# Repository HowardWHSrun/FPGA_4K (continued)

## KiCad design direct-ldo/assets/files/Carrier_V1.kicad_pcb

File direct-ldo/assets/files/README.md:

# Direct LDO Carrier V6 — full KiCad project

Captured 2026-11-01T20:14:21.699674-06:00. Open `Carrier_V1/Carrier_V1.kicad_pro` in KiCad 10.0.6 or newer after extracting the entire ZIP. Keep the PCB, schematic, settings, rules, symbol and footprint libraries, library tables and model folders together.

Four-layer XEM8305 carrier for the existing LDO board. V6 includes the MC2.14–MC2.16 SYSMON reference link. JLC placement, factory acceptance and powered qualification remain pending.

This package includes the complete saved project and available 3D model dependencies. Local model paths are retained or made relative for portability. Historical native filenames and library identifiers remain intact. Editor caches, lock files and automatic backups are excluded. Model coverage and unresolved paths are recorded in `package-manifest.json`; nominal or substitute models are not proof of assembled fit.

Native snapshot: 92 schematic components, 92 PCB footprints, 4 copper layers, 848 track/via objects and 18 copper zones. Check reports: 0 DRC errors, 0 DRC warnings, 0 unconnected-item reports, 0 schematic/PCB parity findings. These are saved-rule CAD checks, not hardware or fabrication qualification; ignored categories remain in the check summary.

Native source and manufacturer identifiers are retained. Existing third-party library and model terms continue to apply; this package grants no new rights to those materials. KiCad library license: https://www.kicad.org/libraries/license/ . Engineering references remain in the schematic and source fields.

[Download full KiCad ZIP](Direct_LDO_Carrier_V6_Full_KiCad.zip) · [Schematic PDF](../schematic-v6.pdf)

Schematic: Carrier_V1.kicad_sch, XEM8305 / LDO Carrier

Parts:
C1: 0.1u 25v; C_0402_1005Metric; Voltage 25V; Tolerance 10%; MPN CL05B104KA5NNNC; LCSC Part # C155422
C2: 220u 25v; CP_Panasonic_EEEFTE221XAL_D6.3x7.7_V3; MPN EEEFTE221XAL; LCSC Part # C1881633
C3: 22u 35V; C_1206_3216Metric; Voltage 35V; Tolerance 20%; MPN C3216X5R1V226MTJ00E; LCSC Part # C342620
C4: 0.1u 25V; C_0402_1005Metric; Voltage 25V; Tolerance 10%; MPN CL05B104KA5NNNC; LCSC Part # C155422
C5: 1u 25V; C_0603_1608Metric; Voltage 25V; Tolerance 10%; MPN CL10A105KA8NNNC; LCSC Part # C5673
C6: 3.3n 50V; C_0402_1005Metric; Voltage 50V; Tolerance 10%; MPN CL05B332KB5NNNC; LCSC Part # C26404
C7: 0.1u 16V; C_0402_1005Metric; Voltage 16V; Tolerance 10%; MPN CL05B104KO5NNNC; LCSC Part # C1525
C8, C9: 22u 10V; C_1206_3216Metric; Voltage 10V; Tolerance 10%; MPN CL31B226KPHNNNE; LCSC Part # C87996
C10: 10p 50V; C_0402_1005Metric; Voltage 50V; Tolerance 5%; MPN CL05C100JB5NNNC; LCSC Part # C32949
C11, C12: 4.7u 10V X5R; C_0402_1005Metric; MPN CL05A475MP5NRNC; LCSC Part # C23733
C13: 4.7u; C_0402_1005Metric; Voltage 10V; MPN CL05A475MP5NRNC; LCSC Part # C23733
C14, C16, C19, C22, C23, C24, C25, C28, C30, C31, C32, C34, C35, C36, C37, C38, C39, C40, C41: 100n; C_0402_1005Metric; Voltage 16V; Tolerance 10%; MPN CL05B104KO5NNNC; LCSC Part # C1525
C17, C18: 18p; C_0402_1005Metric; MPN C0402C180J5GACTU; LCSC Part # C22442494
C20, C33: 10n; C_0402_1005Metric; Voltage 16V; Tolerance 10%; MPN C0402C103K4RACTU; LCSC Part # C2649513
C21, C26, C27, C29: 4.7u; C_0402_1005Metric; Voltage 6.3V; Tolerance 20%; MPN JMK105BBJ475MV-F; LCSC Part # C87147
D1: SMBJ15CA-13-F; D_SMB; MPN SMBJ15CA-13-F; LCSC Part # C135047
D2: 598-8070-107F; LED_0603_1608Metric; MPN 5988070107F; LCSC Part # C6695603
D3: APT1608LZGCK; LED_Kingbright_APT1608LZGCK_V2; Voltage 2.65V typ @2mA; MPN APT1608LZGCK; LCSC Part # C5246833
D4: APT1608LSYCK/J3-PRV; LED_Kingbright_APT1608LSYCK_J3_PRV_V2; Voltage 1.85V typ @2mA; MPN APT1608LSYCK/J3-PRV; LCSC Part # C5246836
FB1, FB3, FB4: 600R; Ferrite_Bead_Murata_BLM18KG601SN1D_0603_V4; MPN BLM18KG601SN1D; LCSC Part # C85833
FB2: 220R @100MHz; BRK8305_A03_FB503; MANUFACTURER_PN BLM21PG221SN1D; LCSC Part # C85840
H1, H2, H3, H4: XEM M3 NPTH; MountingHole_3.2mm_XEM_M3_Keepout
J1: LDO_50DS; Hirose_DF40C(2.0)-50DS-0.4V_2x25_P0.4mm; MPN DF40C(2.0)-50DS-0.4V(51); LCSC Part # C3649428
J2: LDO_24DS; Hirose_DF40C(2.0)-24DS-0.4V_2x12_P0.4mm; MPN DF40C(2.0)-24DS-0.4V(51); LCSC Part # C6539782
J3: PJ-102AH; PJ102AH; MPN PJ-102AH; LCSC Part # C3096093
J4: USB4110-GF-A; USB_C_Receptacle_GCT_USB4110_GF_A_Horizontal; MANUFACTURER_PN USB4110-GF-A; LCSC Part # C5143397
L1: 3.3uH; L_Coilcraft_XAL5030-332MEC; MPN XAL5030-332MEC; LCSC Part # C5342047
MC1: ERF6-50-03.5-L-DV-A-K-TR; MPN ERF6-50-03.5-L-DV-A-K-TR
MC2: XEM_MC2_80; ERF6-40-03.5-L-DV-A-K-TR; MPN ERF6-40-03.5-L-DV-A-K-TR
MC3: XEM_MC3_80; ERF6-40-03.5-L-DV-A-K-TR; MPN ERF6-40-03.5-L-DV-A-K-TR
R1: 2.0k; R_0603_1608Metric; MPN CRCW06032K00FKEAHP; LCSC Part # C313719
R2: 10k 1%; R_0402_1005Metric; MPN CRCW040210K0FKED; LCSC Part # C71617
R3: 73.2k 1%; R_0402_1005Metric; MPN RC0402FR-0773K2L; LCSC Part # C185398
R4: 22.1k 1%; R_0402_1005Metric; MPN RC0402FR-0722K1L; LCSC Part # C163478
R5: 100k; R_0402_1005Metric; MPN ERJ2RKF1003X; LCSC Part # C192169
R6, R7: 5.1k 1%; R_0402_1005Metric; MPN CRCW04025K10FKEDC; LCSC Part # C2076825
R8, R9: 100k; R_0402_1005Metric; Tolerance 1%; MPN CRCW0402100KFKED; LCSC Part # C481918
R10: 2k; R_0402_1005Metric; Tolerance 1%; MPN CRCW04022K00FKED; LCSC Part # C482125
R11, R12: 10k; R_0402_1005Metric; Tolerance 1%; MPN CRCW040210K0FKED; LCSC Part # C71617
R13: 12k 1%; R_0402_1005Metric; Tolerance 1%; MPN CRCW040212K0FKED; LCSC Part # C481938
R14: 3.0k 1%; R_0603_1608Metric; Rating 0603 1% 0.1W minimum; MPN CRCW06033K00FKEA; LCSC Part # C844780
R15: 6.8k 1%; R_0603_1608Metric; Rating 0603 1% 0.1W minimum; MPN CRCW06036K80FKEA; LCSC Part # C844805
TP1: 12V; TestPoint_Pad_D1.5mm
TP2: 3V3_MAIN; TestPoint_Pad_D1.5mm
TP3: 1V5; TestPoint_Pad_D1.5mm
TP4: XEM_1V8; TestPoint_Pad_D1.5mm
TP5: USB_5V; TestPoint_Pad_D1.5mm
TP6: USB_3V3; TestPoint_Pad_D1.5mm
TP7: GND_PWR; TestPoint_Pad_D1.5mm
TP8: GND_USB; TestPoint_Pad_D1.5mm
U1: TPS54429ERSAR; TPS54429E_RSA; MPN TPS54429ERSAR
U2: TLV75515PDRVR; Texas_WSON-6_2x2mm_P0.65mm_EP1x1.6mm_TLV755_DRV_V2; MPN TLV75515PDRVR; LCSC Part # C2868685
U3: FT232HQ; BRK8305_A03_U501; MANUFACTURER_PN FT232HQ-REEL; LCSC Part # C82158
U4, U5, U6, U7: SN74AXC1T45DBVR; BRK8305_A03_U500; MANUFACTURER_PN SN74AXC1T45DBVR; LCSC Part # C2677376
U8: 93LC56BT-E/MS; BRK8305_A03_U505; MANUFACTURER_PN 93LC56BT-E/MS; LCSC Part # C2061196
Y1: 12MHz; BRK8305_A03_Y500; MPN ABM8-12.000MHZ-B2-T; LCSC Part # C596894

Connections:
+1V5: C11.1, MC1.2 (VCCO_64), MC1.4 (VCCO_64), TP3.1, U2.1 (OUT)
+3V3: C8.1, C9.1, C10.1, C12.1, J1.1 (3V3), J1.2 (3V3), L1.2, R3.1, R14.1, TP2.1, U1.16 (VO), U2.6 (IN)
+12V: C1.1, C2.1, C3.1, C4.1, D1.2 (A2), J3.1, MC1.91 (VDCIN), MC1.93 (VDCIN), MC1.95 (VDCIN), MC1.97 (VDCIN), MC1.99 (VDCIN), R1.1, R2.1, TP1.1, U1.13 (VIN1), U1.14 (VIN2), U1.15 (VIN3)
/FB_BUCK: C10.2, R3.2, R4.1, U1.1 (VFB)
/USBJTAG_1.8V_ANALOG: C32.2, U3.37 (VCCA)
/USBJTAG_1.8V_CORE: C31.2, U3.38 (VCORE)
/USBJTAG_3.3V: C19.1, C21.1, C22.1, C23.1, C24.1, C25.1, C26.1, C34.1, C36.1, C38.1, C40.1, FB3.1, FB4.1, R9.1, R11.2, R12.1, TP6.1, U3.12 (VCCIO), U3.24 (VCCIO), U3.39 (VCCD), U3.46 (VCCIO), U4.1 (Vcca), U4.5 (DIR), U5.1 (Vcca), U5.5 (DIR), U6.1 (Vcca), U7.1 (Vcca), U7.5 (DIR), U8.8 (VCC)
/USBJTAG_3.3V_PHY: C29.1, C30.1, FB4.2, U3.3 (VPHY)
/USBJTAG_3.3V_PLL: C27.1, C28.1, FB3.2, U3.8 (VPLL)
/USBJTAG_5V_FILTERED: C13.1, C14.1, FB1.2, U3.40 (VREGIN)
/USBJTAG_EECLK: R9.2, U3.44 (EECLK), U8.2 (CLK)
/USBJTAG_EECS: R8.1, U3.45 (EECS), U8.1 (CS)
/USBJTAG_EEDATA: R10.1, U3.43 (EEDATA), U8.3 (DI)
/XEM_1.8V: C35.1, C37.1, C39.1, C41.1, MC2.75 (1V8_OUT), MC2.77 (1V8_OUT), MC2.79 (1V8_OUT), TP4.1, U4.6 (Vccb), U5.6 (Vccb), U6.6 (Vccb), U7.6 (Vccb)
CHIP_RESET: J1.14 (CHIP_RESET), MC1.75 (B64_L9P)
CLK32MHZ: J1.36 (CLK32MHZ), MC1.67 (B64_L11P_GC)
CLKH: J1.12 (CLKH), MC1.77 (B64_L9N)
D1: J1.4 (D1), MC1.85 (B64_L7N)
D2: J1.6 (D2), MC1.83 (B64_L7P)
D3: J1.8 (D3), MC1.81 (B64_L8N)
D4: J1.10 (D4), MC1.79 (B64_L8P)
D5: J1.38 (D5), MC1.47 (B64_L21P)
D6: J1.40 (D6), MC1.45 (B64_L22N)
D7: J1.42 (D7), MC1.43 (B64_L22P)
D8: J1.44 (D8), MC1.41 (B64_L23N)
FE_RESET: J1.20 (FE_RESET), MC1.69 (B64_L11N_GC)
GND: C1.2, C2.2, C3.2, C4.2, C5.1, C6.1, C8.2, C9.2, C11.2, C12.2, C13.2, C14.2, C16.2, C17.2, C18.2, C19.2, C20.1, C21.2, C22.2, C23.2, C24.2, C25.2, C26.2, C27.2, C28.2, C29.2, C30.2, C31.1, C32.1, C33.2, C34.2, C35.2, C36.2, C37.2, C38.2, C39.2, C40.2, C41.2, D1.1 (A1), D2.1 (K), D3.1 (K), D4.1 (K), FB2.1, J1.49 (DGND), J1.50 (DGND), J3.2, J4.A1 (GND), J4.A12 (GND), J4.B1 (GND), J4.B12 (GND), MC1.5 (DGND), MC1.6 (DGND), MC1.7 (DGND), MC1.8 (DGND), MC1.33 (DGND), MC1.34 (DGND), MC1.61 (DGND), MC1.62 (DGND), MC1.92 (DGND), MC1.94 (DGND), MC1.96 (DGND), MC1.98 (DGND), MC1.100 (DGND), MC2.6 (DGND), MC2.9 (DGND), MC2.20 (DGND), MC2.35 (DGND), MC2.45 (DGND), MC2.46 (DGND), MC2.47 (DGND), MC2.72 (DGND), MC2.73 (DGND), MC2.74 (DGND), MC2.76 (DGND), MC3.1 (DGND), MC3.2 (DGND), MC3.7 (DGND), MC3.8 (DGND), MC3.13 (DGND), MC3.14 (DGND), MC3.19 (DGND), MC3.20 (DGND), MC3.25 (DGND), MC3.26 (DGND), MC3.31 (DGND), MC3.32 (DGND), MC3.37 (DGND), MC3.38 (DGND), MC3.43 (DGND), MC3.44 (DGND), MC3.49 (DGND), MC3.50 (DGND), MC3.55 (DGND), MC3.56 (DGND), MC3.61 (DGND), MC3.62 (DGND), MC3.67 (DGND), MC3.68 (DGND), MC3.73 (DGND), MC3.74 (DGND), MC3.79 (DGND), MC3.80 (DGND), R4.2, R5.2, R6.1, R7.2, R8.2, R13.2, TP7.1, TP8.1, U1.4 (GND), U1.7 (PGND1), U1.8 (PGND2), U1.17 (EP/PGND), U2.3 (GND), U2.7 (EP), U3.4 (AGND), U3.9 (AGND), U3.10 (GND), U3.11 (GND), U3.22 (GND), U3.23 (GND), U3.35 (GND), U3.36 (GND), U3.41 (AGND), U3.42 (TEST), U3.47 (GND), U3.48 (GND), U3.PAD, U4.2 (GND), U5.2 (GND), U6.2 (GND), U6.5 (DIR), U7.2 (GND), U8.5 (VSS), Y1.2 (CASE), Y1.4 (CASE)
IMP_TEST: J1.18 (IMP_TEST), MC1.71 (B64_L10P)
JTAG_TCK_1.8V: MC2.1 (JTAG_TCK), U4.4 (B)
JTAG_TDI_1.8V: MC2.3 (JTAG_TDI), U5.4 (B)
JTAG_TDO_1.8V: MC2.7 (JTAG_TDO), U6.4 (B)
JTAG_TMS_1.8V: MC2.5 (JTAG_TMS), U7.4 (B)
unnamed: C16.1, FB2.2, J4.M1 (SHELL), J4.M2 (SHELL), J4.M3 (SHELL), J4.M4 (SHELL)
unnamed: D2.2 (A), R1.2
unnamed: D3.2 (A), R14.2
unnamed: D4.2 (A), R15.2
unnamed: J4.A5 (CC1), R6.2
unnamed: J4.B5 (CC2), R7.1
unnamed: MC2.14 (VREFP), MC2.16 (GNDADC)
unnamed: R2.2, U1.6 (EN)
unnamed: C6.2, U1.3 (SS)
unnamed: C7.2, L1.1, U1.9 (SW1), U1.10 (SW2), U1.11 (SW3)
unnamed: C7.1, U1.12 (VBST)
unnamed: C5.2, U1.2 (VREG5)
unnamed: U3.13 (ADBUS0_/_TCK_/_SK), U4.3 (A)
unnamed: U3.14 (ADBUS1_/_TDI_/_DO), U5.3 (A)
unnamed: U3.15 (ADBUS2_/_TDO_/_DI), U6.3 (A)
unnamed: U3.16 (ADBUS3_/_TMS_/_CS), U7.3 (A)
unnamed: C17.1, U3.1 (OSCI), Y1.1 (OSC1)
unnamed: C18.1, U3.2 (OSCO), Y1.3 (OSC2)
unnamed: R13.1, U3.5 (REF)
unnamed: C33.1, R12.2, U3.34 (~RESET)
unnamed: R10.2, R11.1, U8.4 (DO)
READ: J1.46 (READ), MC1.39 (B64_L23P)
SPI_CLK: J1.22 (SPI_CLK), MC1.49 (B64_L21N)
SPI_DINL: J1.26 (SPI_DINL), MC1.63 (B64_L12P_GC)
SPI_DINR: J1.28 (SPI_DINR), MC1.57 (B64_L19N)
SPI_LATCH: J1.24 (SPI_LATCH), MC1.65 (B64_L12N_GC)
STIM_CHB: J1.33 (STIM_CHB), MC1.37 (B64_L24N)
STIM_CLK: J1.29 (STIM_CLK), MC1.55 (B64_L19P)
STIM_EN: J1.31 (STIM_EN), MC1.53 (B64_L20N)
STIM_START: J1.27 (STIM_START), MC1.73 (B64_L10N)
SYNC: J1.34 (SYNC), MC1.51 (B64_L20P)
USBJTAG_5V_IN: C20.2, FB1.1, J4.A4 (VBUS), J4.A9 (VBUS), J4.B4 (VBUS), J4.B9 (VBUS), R15.1, TP5.1
USB_D_N: J4.A7 (DN1), J4.B7 (DN2), U3.6 (DM)
USB_D_P: J4.A6 (DP1), J4.B6 (DP2), U3.7 (DP)
XEM PG: MC1.90 (XEM8305_PG), R5.1, U2.4 (EN)

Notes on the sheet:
Vin_12V
Function: U7 translates TMS from FTDI3.3V to XEM1.8V. Source / changes: Opal Kelly BRK8305 A03,25Oct2023, JTAG sheet8/PDFp4: U504/C525/C526 -> U7/C40/C41. https://pins.opalkelly.com/downloads/583/download?category_id=3 Same SN74AXC1T45DBVR and two100nF values; topology unchanged. Codex redraw follo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
Function: U5 translates TDI from FTDI3.3V to XEM1.8V. Source / changes: Opal Kelly BRK8305 A03,25Oct2023, JTAG sheet8/PDFp4: U502/C515/C516 -> U5/C36/C37. https://pins.opalkelly.com/downloads/583/download?category_id=3 Same SN74AXC1T45DBVR and two100nF values; topology unchanged. Codex redraw follo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
Function: U1 converts 12 V to the main carrier 3.3 V rail. R3/R4/C10 form its feedback network. TP2 probes 3.3 V after L1; TP3 probes 1.5 V. D3/R14 indicate voltage presence (about 0.3 mA nominal), not power-good status. U2 derives 1.5 V from 3.3 V when enabled by XEM_PG. Source / changes: Inherite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
VBuck_3.3V
Function: J4 is a horizontal USB2 device socket; cable entry is parallel to the PCB. R6/R7 are CC pulldowns; C16/FB2 connect shield to GND at high frequency. Source / changes: GCT USB4110-GF-A, USB4110 revB4,22May2024,sheet1/2: https://gct.co/files/drawings/usb4110.pdf Codex adapts BRK8305 A03,25Oc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
Function: U6 translates TDO from XEM1.8V to FTDI3.3V. Source / changes: Opal Kelly BRK8305 A03,25Oct2023, JTAG sheet8/PDFp4: U503/C519/C520 -> U6/C38/C39. https://pins.opalkelly.com/downloads/583/download?category_id=3 Same SN74AXC1T45DBVR and two100nF values; topology unchanged. Codex redraw follo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
Level shifters (BRK8305 style)
Function: J3 receives barrel-jack12V. C2 stores input charge; C1 bypasses XEM12V. D1 shunts transients. R1/D2 indicate input voltage; TP1/TP7 provide12V/GND probe access. Source / changes: Inherited carrier input structure; original author/reference is not established. V6 changed placement/copper, 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
Function: D4 shows rawUSB5V; R15=6.8kohm retains about0.47mA typical LED load. TP5=rawUSB5V; TP6=FTDI3.3V; TP8=GND. Source / changes: Codex probe/LED branch; V2 APT1608LSYCK/J3-PRV replaces AA1608LSYSK. R15 value and all electrical connections retained. Kingbright DSAN8389,V5B,6Jan2021,p1land/ pola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
Connectors + Xem 1.8v
Function: H1-H4 align carrier mounting holes to XEM8305. Source / changes: Opal Kelly XEM8305-AXX Mechanical Drawing, PCB Revision AXX,sheet1, and XEM8305 Mating Board Diagram, sheet1; dimensionsmm. https://docs.opalkelly.com/xem8305/specifications/ Codex registration Xcarrier=101+Ymodule,Ycarrier=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
Function: U4 translates TCK from FTDI3.3V to XEM1.8V. Source / changes: Opal Kelly BRK8305 A03,25Oct2023, JTAG sheet8/PDFp4: U500/C503/C504 -> U4/C34/C35. https://pins.opalkelly.com/downloads/583/download?category_id=3 Same SN74AXC1T45DBVR and two100nF values; topology unchanged. Codex redraw follo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
Function: TP4 probes the module-sourced1.8V translator supply. Source / changes: Codex adds one passive pad at C35 rail. Opal Kelly XEM8305 Expansion Connectors /1.8V Power Supply: https://docs.opalkelly.com/xem8305/expansion-connectors/ No LED/load added to this rail or FTDI internal1.8V nodes.
Function: MC1 links XEM8305 Bank64 to LDO J1. CLK32MHZ: J1.36 -> MC1.67 -> AD21 (positive GC). SPI_CLK: J1.22 <- MC1.49 <- AB20 (FPGA output). Bank64 uses 1.5 V. Other 21 signal assignments unchanged. Source / changes: Codex clock-pin swap, 25 October 2026. Inherited carrier structure; only MC1.49 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
Function: U3 converts USB2 to JTAG through its MPSSE engine. Y1 is its12MHz reference; U8 stores optional USB identity/configuration. Local capacitors bypass each supply; FB1/FB3/FB4 separate the shown rail branches. Source / changes: inherited Opal Kelly BRK8305 A03,25Oct2023,JTAG sheet8/ PDFp4; l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
Function: Short MC2.14 (VREFP) to MC2.16 (GNDADC) to select the XEM8305 internal SYSMON ADC reference. Source / changes: Opal Kelly XEM8305, Expansion Connectors, SYSMON; web page accessed 31 Oct 2026: https://docs.opalkelly.com/xem8305/expansion-connectors/ Codex V6 adds direct copper instead of a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

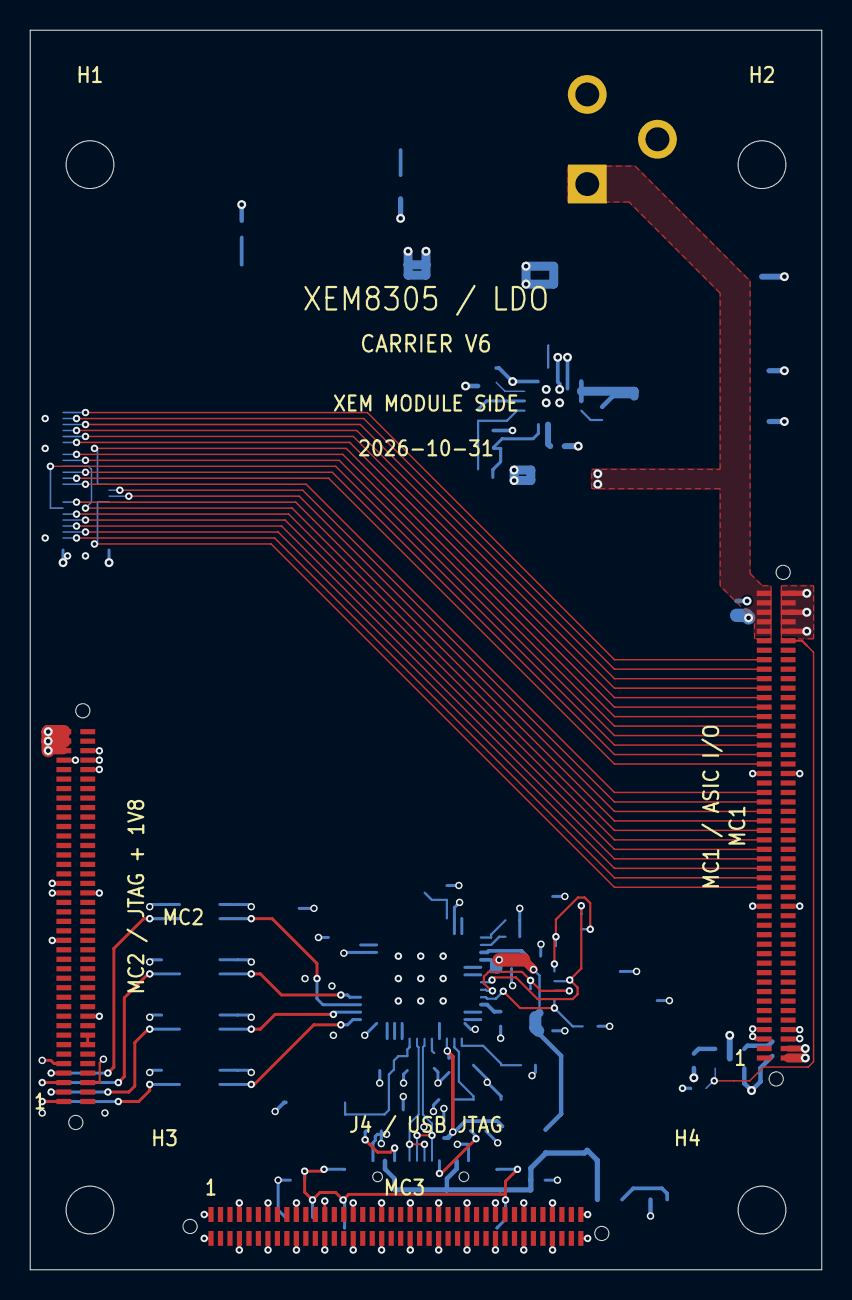
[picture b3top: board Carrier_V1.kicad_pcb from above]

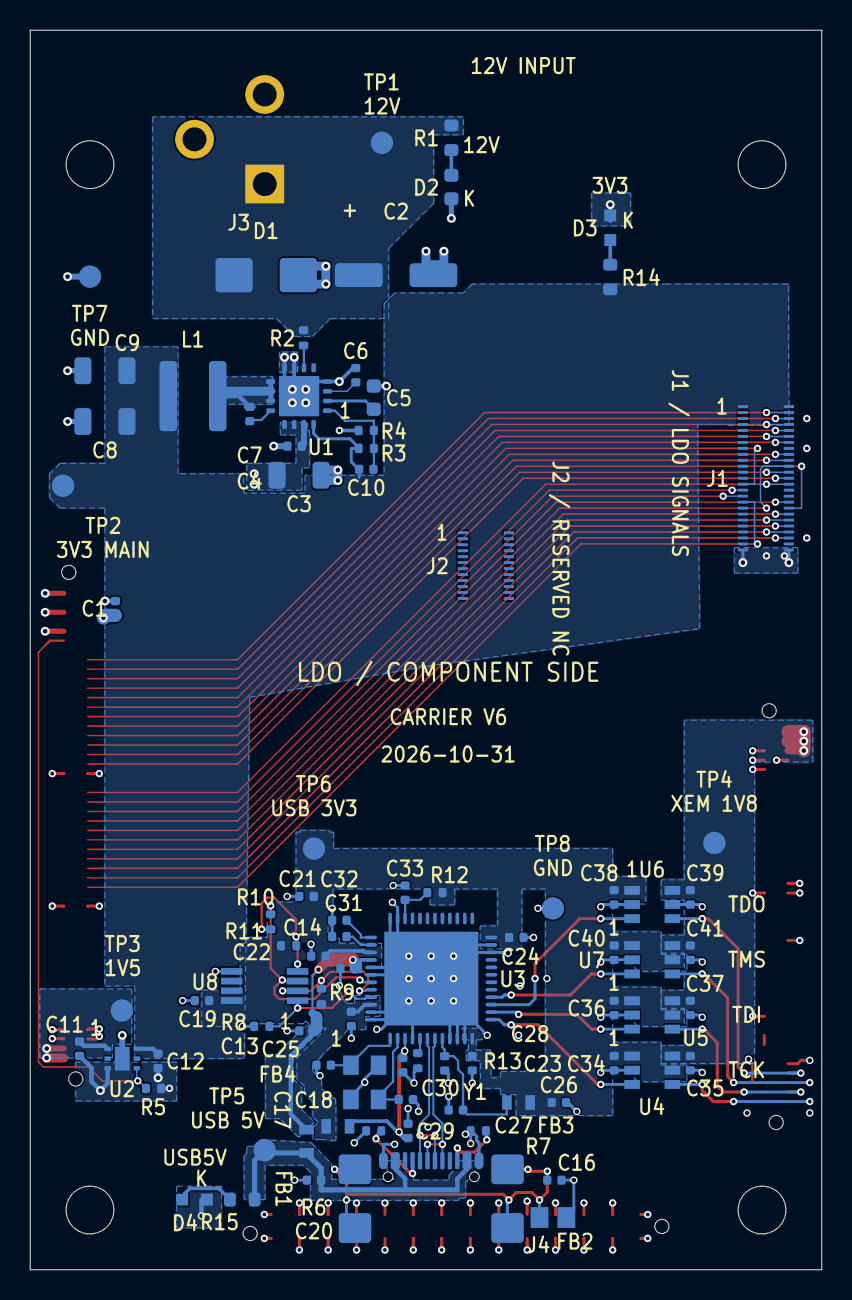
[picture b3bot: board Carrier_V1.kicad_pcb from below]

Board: 4 copper layers, 53.0 x 83.0 mm, 92 parts (85 on the bottom side), 67 nets.
